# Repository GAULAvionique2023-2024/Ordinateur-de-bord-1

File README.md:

# ODB 1

## Description of the flight computer 1:
This board is an updated version of the first flight controler with little extra. So basicly I copy the old desing that it was an arduino shield and made it a standalone board. All the sensor is part of the board too, so no more module.All this help to make a board much smaller and more reliable. In extra I add a latching circuit too arme the board. You need to hold the button 3sec to power up the circuit and same thing to power it off. All switching is made with an mosfet so no mecanical switching excluding the power button. So the vibration can't make or break a connection and this is why the push button have an latching circuit, too avoid a false triger. Moreover I add a circuit too datalog the data on an SD card,I made a test circuit to test the 2 pyro. The circuit pass a little current (40mA) in the fuse and we mesure the voltage after so we can test for a short or open fuse. We can use this same circuit after to valid an ignition. I also add a logic circuit too avoid to put main power in the pyro when we trigger the test. It need 2 mosfet to be activate to ignite the fuse. A buzzer and a led status is also added. The board is powerd by a usb or lipo 1S(3.7v) that it can be charge by usb on the board. The RFD900 is powered by usb if its available but we will not be able to use full power only on usb so this is for testing only, on normal condition we will use an lipo 3S(11.1v). The pyro is powered by an lipo 4S(14.8v).

## Update log

### 23/12/16
All the test is now done. I corrected some mistake and change the status LED for an RGB one so it will be easier to understand its meaning. The new board its on the way.

### 23/11/22
Long time no see. Well I receive the board and do some test. All work except the GYRO and the inition of the fuse need to be confirm. I think I broke the gyro when I solder it so am waiting for a new one and in the same time im waiting for some e-fuse. I also made some minor change in the schematic and the board desing. Like switching the green status led by an RGB led, so it will be easyer to understand some status.  

### 23/10/09
Now the pcb is finish. I add the BOM file and the pcb is now on production.(see image: [ODB1_PCB](https://github.com/GAULAvionique2023-2024/Ordinateur-de-bord-1/blob/main/Images/ODB1_PCB.png))

### 23/10/01
So I rework the schematic to use less components and had the crystal circut, cause I dont know how but I was forgeting it. I also begin to layout the components on the pcb (see image: [OBD1_1_10_23](https://github.com/GAULAvionique2023-2024/Ordinateur-de-bord-1/blob/main/Images/OBD1_1_10_23.png)). I try my best to fit in the 85mmx85mm.

### 23/09/23
I add the possibility to use the RFD900 with the USB.

### 23/09/22
I can say that the schematic is now done but it will need to be verified to but sure that everything is ok and avoid poor mistake.
1.Redesing of the logic circuit protection to be more secure
2.Add a different batteries for the RFD900 so if the RFD900 drain it the pyro still have its own power.
3.In link with the second point, now the pyro is on 4s lipo (14.8v)

### 23/09/17
The schematic is almost done. Need to retink of some part of the logic part to protect the pyro cause it look like it can cause an oscilation (this part is not even up to date)
1.Add a buzzer.
2.Add poly fuse.
3.Add the logic circuit to protect the pyro. (see note on top)
4.Add latching circuit. (Hold 3s to power on/off)
5.Add many status leds. (one led can be placed externaly by a screw terminal)

This week I will try to list all the feature of this board, finalyze the schematic, add the data sheets of some ICs.

## Features
* Standalone board
* Powered by usb or lipo 1S
* Lipo charger in board
* Self test on igniter
* 2 ignitions circuits
* Gyro/Baro in board
* SD card for dataloging
* Latching circuit for powered the circuit
## Documentation
This is a list of documentation for the Ic

* [STM32F103C8](https://www.st.com/resource/en/datasheet/stm32f103c8.pdf) Main  microcontroller
* [ICM-20602](https://invensense.tdk.com/wp-content/uploads/2016/10/DS-000176-ICM-20602-v1.0.pdf) High Performance 6-Axis MEMS
* [BMP280](https://www.bosch-sensortec.com/media/boschsensortec/downloads/datasheets/bst-bmp280-ds001.pdf) Digital pressure sensor
* [L76L-M33](https://github.com/ul-gaul/Nebula-2022-2023/blob/cef41a131481a57f440abe9ede77973086518a58/WIP/Documentation/Quectel_L76_Series_Hardware_Design_V3.1.pdf) GNSS Module (GPS)
* [GT-0930RP2](https://github.com/ul-gaul/Nebula-2022-2023/blob/aa67e142a6133a87d8f8f1008be1e9982ea42536/WIP/Documentation/GT-0930RP2-14-Feb-2019.pdf) Buzzer
* [HM-10](https://github.com/ul-gaul/Nebula-2022-2023/blob/aa67e142a6133a87d8f8f1008be1e9982ea42536/WIP/Documentation/11.%20HM10%20BLE_FTDI.pdf)  BLE Module
* [TPS61201DRCR](https://www.ti.com/lit/ds/symlink/tps61201.pdf?ts=1695532721814&ref_url=https%253A%252F%252Fwww.ti.com%252Fproduct%252FTPS61201%252Fpart-details%252FTPS61201DRCR)  Low Input Voltage Synchronous Boost Converter
* [LM1085](https://www.ti.com/lit/ds/symlink/lm1085.pdf?ts=1695467476779&ref_url=https%253A%252F%252Fwww.ti.com%252Fproduct%252FLM1085%252Fpart-details%252FLM1085ISX-3.3%252FNOPB) 3-A Low Dropout Positive Regulators
* [max1898eub42+T](https://www.analog.com/media/en/technical-documentation/data-sheets/max1898.pdf) Linear Charger for Single-Cell Li+ Battery
* [LTC2954ITS8-1](https://www.analog.com/media/en/technical-documentation/data-sheets/2954fb.pdf) Pushbutton On/Off Controller with µP Interrup
* [CD74HC4051-EP](https://www.ti.com/lit/ds/symlink/cd74hc4051-ep.pdf?ts=1695467019480&ref_url=https%253A%252F%252Fwww.google.com%252F) Analog Multiplexer and Demultiplexer
* [74HC2G86DP_125](https://assets.nexperia.com/documents/data-sheet/74HC_HCT2G86.pdf) Dual 2-input EXCLUSIVE-OR gate
* [74HC2G86DP_125](https://assets.nexperia.com/documents/data-sheet/74HC_HCT2G08.pdf) Dual 2-input AND gate
* [74HC2G86DP_125](https://assets.nexperia.com/documents/data-sheet/74LVC2G02.pdf) Dual 2-input NOR gate

## Authors
List of authors
- [@Luka Dupuis](https://github.com/bestrider14)

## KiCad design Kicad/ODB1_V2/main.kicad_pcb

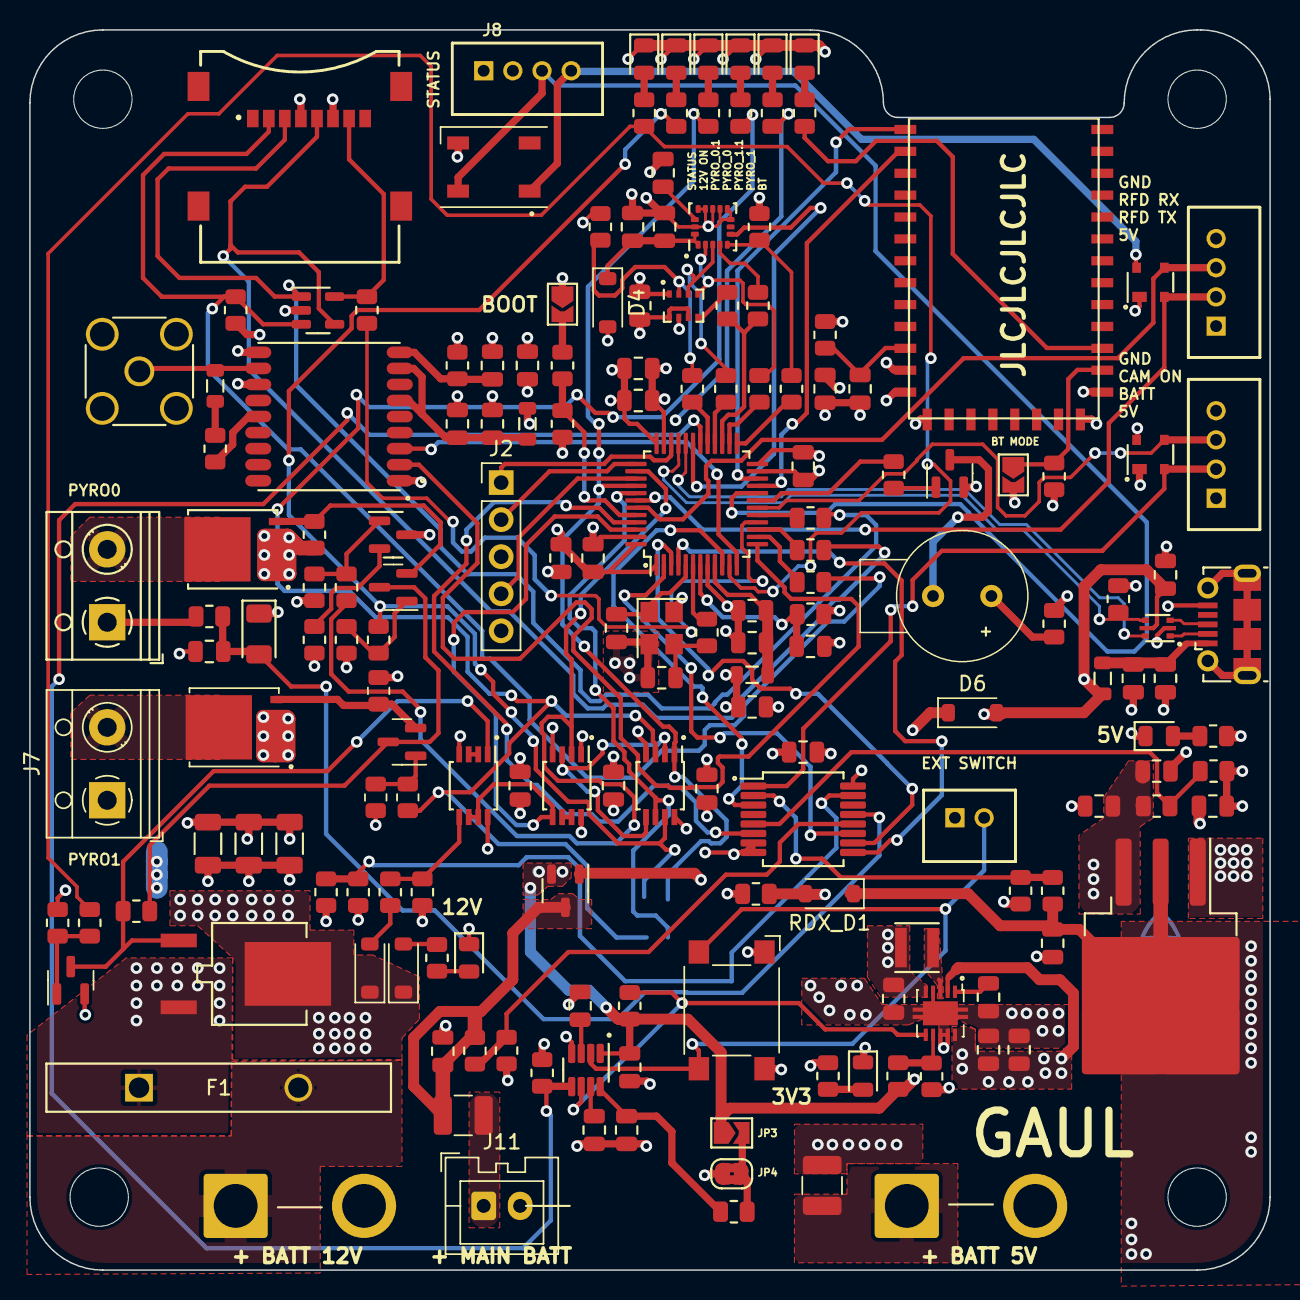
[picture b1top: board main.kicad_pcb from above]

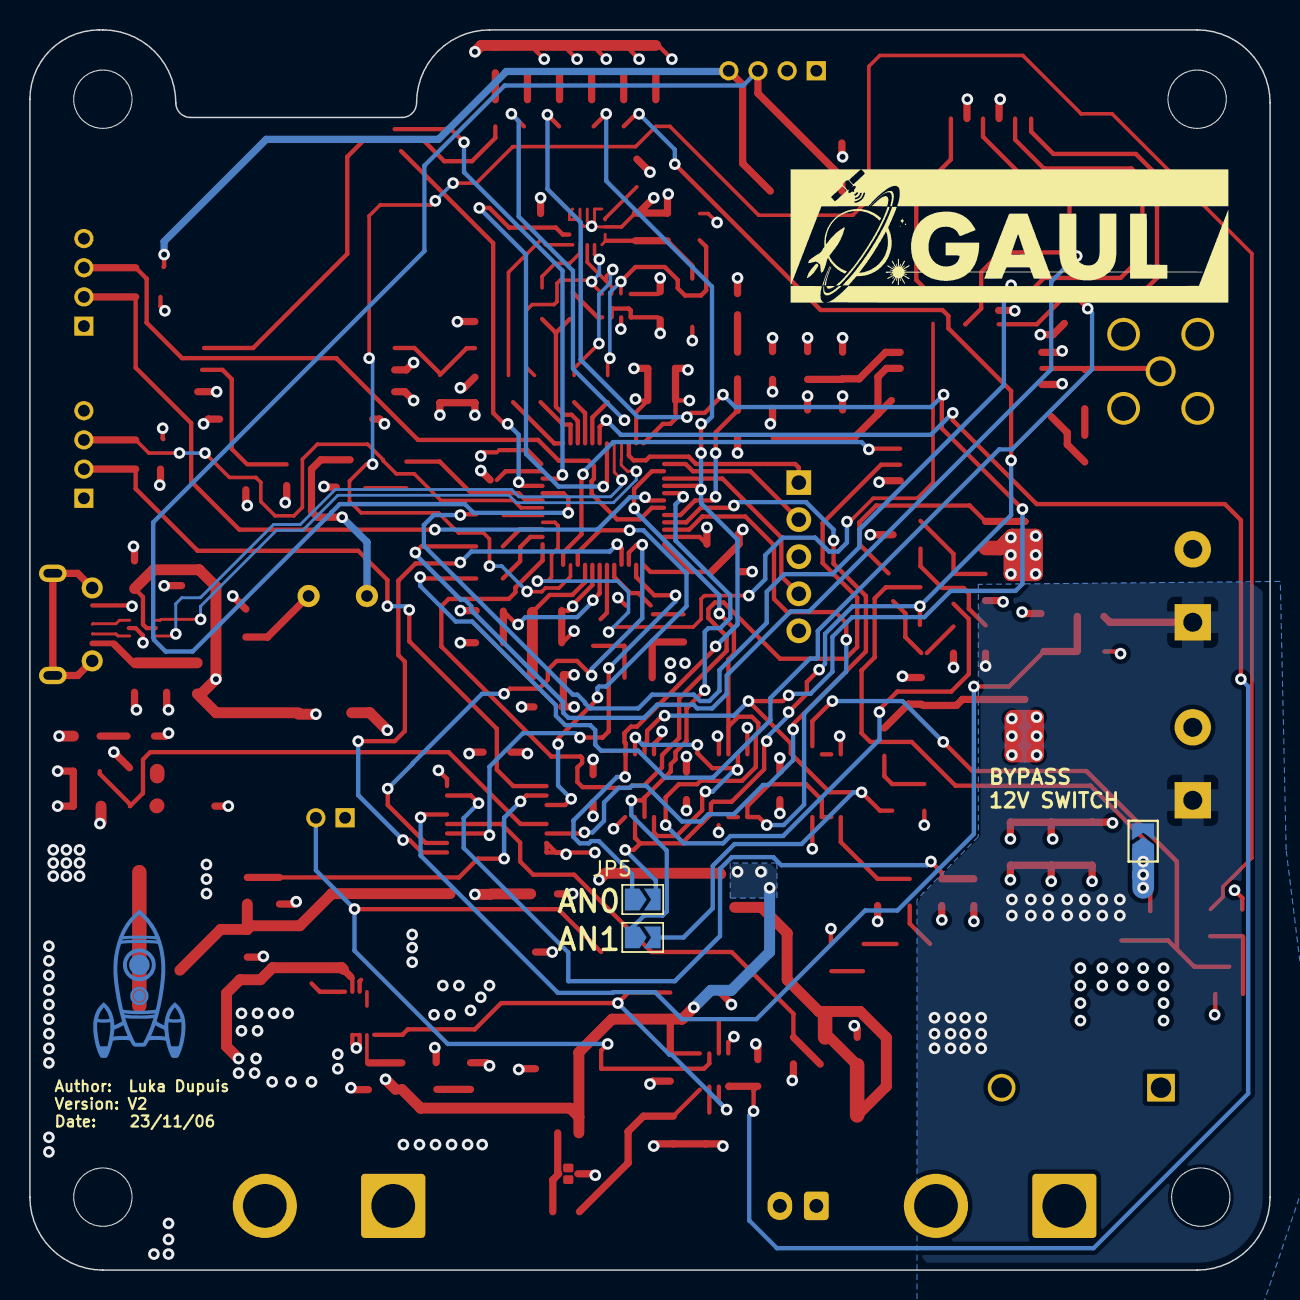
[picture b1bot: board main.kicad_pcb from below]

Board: 4 copper layers, 85.0 x 85.0 mm, 183 parts (3 on the bottom side), 122 nets.

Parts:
5V_R1: 56k; R_0805_2012Metric
5V_R2: 100k; R_0805_2012Metric
5V_R3: 1k5; R_0805_2012Metric
BATT1S_R13, BATT3S2_R12, BATT3S_R9: 100k; R_0805_2012Metric
BATT1S_R14: 27k; R_0805_2012Metric
BATT3S2_Q2: MMBT3904-TP; SOT-23
BATT3S2_R1, BATT3S2_R3, BATT3S2_R4, BATT3S2_R5: 10k; R_0805_2012Metric
BATT3S2_R2, BATT3S2_R6, BATT3S2_R7: 1k5; R_0805_2012Metric
BATT3S2_R11, BATT3S_R8: 36k; R_0805_2012Metric
BMP_C1: 10nf; C_0805_2012Metric
BMP_R1: 10k; R_0805_2012Metric
BMP_R2, BMP_R3: 10R; R_0805_2012Metric
BT_C1: 100nf; C_0805_2012Metric
BT_C2: 10uf; C_0805_2012Metric
BT_R1, BT_R2: 1k5; R_0805_2012Metric
BT_R3: 10k; R_0805_2012Metric
BUZ_R1: 1k5; R_0805_2012Metric
BUZ_R2: 30R; R_0805_2012Metric
BZ1: Buzzer; GT-0930RP2
C1: 10uf; C_0805_2012Metric
D1, D2: SP0503BAHTG; SOT-143
D3, D16: MMSZ4691-TP; D_SOD-123
D4, D6: B260A-13-F; D_SOD-123
D5: WS2812B; LED_WS2812B_PLCC4_5.0x5.0mm_P3.2mm
D8: SP0504BAHTG; SOT-23-5
E1: HM-10; 26.9X13X2.2_BOARD
F1: RGEF1400; FUS_RGEF1400_TYCO_TYC
F2, F3: 0ZCH0075AF2E (750ma); Fuse_1210_3225Metric
FB1, FB2, FB3: 120R; L_0805_2012Metric
GPS_C1, GPS_C3: 10uf; C_0805_2012Metric
GPS_C2, GPS_C4: 100nf; C_0805_2012Metric
GPS_R1: 10k; R_0805_2012Metric
GPS_R2: 10R; R_0805_2012Metric
H1, H2, H3, H4: MountingHole; MountingHole_4mm
ICM_C1, ICM_C4, ICM_C5: 100nf; C_0805_2012Metric
ICM_C2, ICM_C7: 10uf; C_0805_2012Metric
ICM_C6: 1uf; C_0805_2012Metric
ICM_R1: 10k; R_0805_2012Metric
ICM_R2, ICM_R3: 10R; R_0805_2012Metric
J1: RFD900; B4B-PH-K
J2: Conn_01x05_Socket; PinHeader_1x05_P2.54mm_Vertical
J3: USB_B_Micro; USB_Micro-B_Molex-105017-0001
J4: MEM2067-02-180-00-A_REVB; GCT_MEM2067-02-180-00-A_REVB
J5: RF2-04A-T-00-50-G; SMA_Wurth_60312002114503_Vertical
J6: PYRO0; TerminalBlock_RND_205-00012_1x02_P5.00mm_Horizontal
J7: PYRO1; TerminalBlock_RND_205-00012_1x02_P5.00mm_Horizontal
J8, J13: CAM; B4B-PH-K
J9: BATT3S1; SolderWire-2.5sqmm_1x02_P8.8mm_D2.4mm_OD4.4mm
J10: BATT12V; SolderWire-2.5sqmm_1x02_P8.8mm_D2.4mm_OD4.4mm
J11: BATT1S; JST_XA_B02B-XASK-1_1x02_P2.50mm_Vertical
J12: EXT_SW; B2B-PH-K
JP1, JP2, JP3, JP5, JP6, JP7: SolderJumper_2_Open; SolderJumper-2_P1.3mm_Open_TrianglePad1.0x1.5mm
JP4: SolderJumper_2_Bridged; SolderJumper-2_P1.3mm_Bridged2Bar_RoundedPad1.0x1.5mm
L1: 100nH; L_0805_2012Metric
LED_3S2_ON1, LED_3V3, LED_5V1, LED_14V8: GREEN; LED_0805_2012Metric
LED_BT1: GREEN; LED_0805_2012Metric
LED_PYRO_0, LED_PYRO_0.1, LED_PYRO_1, LED_PYRO_1.1: GREEN; LED_0805_2012Metric
LPWR_L1: 3.3uH; IND_LQH3NPN3R3MMEL
LTC_C1, LTC_C2: 100nf; C_0805_2012Metric
LTC_C3, LTC_C4: 0.47uf; C_0805_2012Metric
LTC_R1, LTC_R2, LTC_R3: 10k; R_0805_2012Metric
NRST_C1: 100nf; C_0805_2012Metric
PWR_C1: 33uf; C_0805_2012Metric
PWR_C2, PWR_C4, PWR_C5: 10uf; C_0805_2012Metric
PWR_C3, PWR_C8, PWR_C9, PWR_C11: 100nf; C_0805_2012Metric
PWR_C6: 10uf; C_1206_3216Metric
PWR_C7: 100nf; C_1206_3216Metric
PWR_C10: 33uf; C_1206_3216Metric
PWR_R1: 1k5; R_0805_2012Metric
PWR_R2: 1.87M; R_0805_2012Metric
PWR_R3: 249k; R_0805_2012Metric
PYRO_Q3, PYRO_Q211: MMBT3904-TP; SOT-23
PYR_C1, PYR_C3, PYR_C4, PYR_C5, PYR_C6: 100nf; C_0805_2012Metric
PYR_D1: SM5817PL-TP; D_1206_3216Metric
PYR_R2, PYR_R6, PYR_R9, PYR_R13, PYR_R14, PYR_R15, PYR_R16: 1k5; R_0805_2012Metric
PYR_R3, PYR_R5, PYR_R17, PYR_R18, PYR_R19: 10k; R_0805_2012Metric
PYR_R4: 130R 1%; R_0805_2012Metric
PYR_R7: 56k; R_0805_2012Metric
Q2: PMOS; SOT-23-3
Q3, Q8: CSD17310Q5A; TDSON-8-1
Q4: MMBT3904; SOT-23
Q5: IRFR5505TRPBF; PG-TO252AA_INF
Q6: BC857; SOT-23
R2: 100k; R_0805_2012Metric
RDX_D1: B260A-13-F; D_SOD-123
RSTM_R2: 1k5; R_0805_2012Metric
SDC_R1: 10k; R_0805_2012Metric
SDC_R2, SDC_R3, SDC_R4, SDC_R5: 10R; R_0805_2012Metric
SPI_R2, SPI_R3: 10R; R_0805_2012Metric
STM_C1, STM_C6: 10uf; C_0805_2012Metric
STM_C2, STM_C3, STM_C4, STM_C5: 100nf; C_0805_2012Metric
STM_C7, STM_C8: 10nf; C_0805_2012Metric
STM_C9, STM_C10: 6p; C_0805_2012Metric
STM_R1, STM_R3: 10k; R_0805_2012Metric
STM_R4: 30R; R_0805_2012Metric
SW1: POWER BUTTON; SW_SPST_Omron_B3FS-105xP
U1: STM32F103CBT6; LQFP-48_7x7mm_P0.5mm
U2: ICM-20602; LGA-16_3x3mm_P0.5mm_LayoutBorder3x5y
U3: BMP280; Bosch_LGA-8_2x2.5mm_P0.65mm_ClockwisePinNumbering
U4: L76L-M33; GNSS-MODULE_L76L-M33
U5: TPS61201DRCR; VSON-10-1EP_3x3mm_P0.5mm_EP1.65x2.4mm
U7: 74HC4051; SSOP-16_5.3x6.2mm_P0.65mm
U8: LM1085-5.0; TO-263-3_TabPin2
U9: 74HC2G08DP,125; TSSOP-8_3x3mm_P0.65mm
U10: 74LVC2G02DP,125; TSSOP-8_3x3mm_P0.65mm
U11: LTC2954ITS8-1; TSOT-23-8
U12: USBLC6-2P6; SOT-666
U13: 74HC2G86DP_125; TSSOP-8_3x3mm_P0.65mm
USB_R1: 1k5; R_0805_2012Metric
Y1: 16mhz; Crystal_SMD_3225-4Pin_3.2x2.5mm

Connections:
3V3_EN: LTC_R1.1, U5.6 (EN), U11.6 (EN)
5V_AN: 5V_R1.2, 5V_R2.2, U7.2 (A6)
12V_CHECK: U1.46 (PB9), U10.6 (2B), U10.7 (1Y), U13.5 (2A)
+3.3VA: FB3.1, STM_C6.2, STM_C7.2, U1.9 (VDDA)
+3V3: BMP_C1.1, BMP_R1.1, BT_C2.1, BT_R2.2, BT_R3.1, BUZ_R2.1, D4.2 (A), E1.12 (+3.3V), FB1.2, FB3.2, GPS_C3.2, GPS_R1.2, ICM_R1.1, J2.3, J4.4 (VDD), JP1.1 (A), JP4.1 (A), LTC_R3.1, PWR_C1.1, PWR_C8.1, PWR_R1.1, PYR_C3.1, PYR_C4.1, PYR_C5.2, PYR_C6.1, PYR_D1.1 (K), PYR_R5.1, Q6.3 (C), SDC_R1.2, STM_C1.2, STM_C2.2, STM_C3.2, STM_C4.2, STM_C5.2, STM_C8.2, STM_R1.2, U1.1 (VBAT), U1.24 (VDD), U1.36 (VDD), U1.48 (VDD), U3.6 (VDDIO), U3.8 (VDD), U5.2 (VOUT), U5.10 (FB), U7.16 (VCC), U9.8 (VCC), U10.8 (VCC), U13.1 (1A), U13.8 (VCC), USB_R1.2
+5V: 5V_R1.1, 5V_R3.1, D1.4 (K), D2.4 (K), D5.1 (VDD), J1.1, J8.4, J13.1, PWR_C5.1, PWR_C11.1, RDX_D1.1 (K), U8.2 (VO)
+12C: BATT3S2_R1.1, BATT3S2_R12.2, F1.1, JP6.1 (A), PWR_C6.1, PWR_C7.1, PWR_C10.1, PYRO_Q3.3 (C), PYRO_Q211.3 (C), Q5.3 (S)
+12P: BATT3S_R9.2, F3.1, PWR_C4.1, PWR_C9.1, U8.3 (VI)
+12V: D3.1 (K), D16.1 (K), J6.1, J7.1, JP6.2 (B), PYR_R4.1, PYR_R7.1, Q5.2 (D)
+BATT: BATT1S_R14.2, C1.1, F2.1, Q2.3 (D)
/Power/12IN: F1.2, J10.1
BATT3S2_ON: BATT3S2_R2.1, BATT3S2_R7.1, U1.11 (PA1)
BATT_CAM: D2.2 (K), J13.2, U7.1 (A4)
BATT_LIPO1S_AN: BATT1S_R13.2, BATT1S_R14.1, U7.12 (A3)
BATT_LIPO3S2_AN: BATT3S2_R11.2, BATT3S2_R12.1, U7.15 (A2)
BATT_LIPO3S_AN: BATT3S_R8.2, BATT3S_R9.1, U7.5 (A5)
BMP_CS: BMP_R1.2, BMP_R2.2, U3.2 (CSB)
BOOT0: RSTM_R2.1, STM_R3.2, U1.44 (BOOT0)
BT_RX: E1.1 (UART_TX), U1.22 (PB11)
BT_TX: E1.2 (UART_RX), U1.21 (PB10)
BUTTON_INT: LTC_R3.2, U1.30 (PA9), U11.5 (*INT)
BUZZER: BUZ_R1.1, U1.19 (PB1)
CAM_ON: D2.3 (K), J13.3, U1.18 (PB0)
FLIP_FLOP_RST: BATT3S2_R1.2, Q4.3 (C), Q5.1 (G), U10.1 (1A)
FLIP_FLOP_SET: BATT3S2_R4.1, BATT3S2_R5.1, U10.5 (2A)
GND: 5V_R2.1, BATT1S_R13.1, BATT3S2_Q2.2 (E), BATT3S2_R3.1, BATT3S2_R5.2, BATT3S2_R11.1, BATT3S_R8.1, BMP_C1.2, BT_C1.2, BT_C2.2, C1.2, D1.1 (A), D2.1 (A), D5.3 (VSS), D8.2 (A), E1.13 (GND), E1.14 (GND), E1.21 (GND), E1.22 (GND), GPS_C1.1, GPS_C2.1, GPS_C3.1, GPS_C4.1, ICM_C1.1, ICM_C2.1, ICM_C4.2, ICM_C5.1, ICM_C6.1, ICM_C7.1, J1.4, J2.5, J3.5 (GND), J4.6 (VSS), J5.2 (Ext), J8.2, J9.2, J10.2, J11.2, J12.1, J13.4, JP2.2 (B), LED_3S2_ON1.1 (K), LED_3V3.1 (K), LED_5V1.1 (K), LED_14V8.1 (K), LED_BT1.1 (K), LED_PYRO_0.1 (K), LED_PYRO_0.1.1 (K), LED_PYRO_1.1 (K), LED_PYRO_1.1.1 (K), LTC_C1.2, LTC_C2.2, LTC_C3.2, LTC_C4.2, NRST_C1.2, PWR_C1.2, PWR_C2.2, PWR_C3.2, PWR_C4.2, PWR_C5.2, PWR_C6.2, PWR_C7.2, PWR_C8.2, PWR_C9.2, PWR_C10.2, PWR_C11.2, PWR_R3.2, PYR_C1.2, PYR_C3.2, PYR_C4.2, PYR_C5.1, PYR_C6.2, PYR_R3.1, PYR_R17.1, PYR_R18.1, PYR_R19.1, Q3.1 (S), Q3.2 (S), Q3.3 (S), Q4.2 (E), Q8.1 (S), Q8.2 (S), Q8.3 (S), R2.2, STM_C1.1, STM_C2.1, STM_C3.1, STM_C4.1, STM_C5.1, STM_C6.1, STM_C7.1, STM_C8.1, STM_C9.1, STM_C10.1, STM_R3.1, SW1.1, U1.8 (VSSA), U1.23 (VSS), U1.35 (VSS), U1.47 (VSS), U2.8 (FSYNC), U2.9 (GND), U2.10 (GND), U2.11 (GND), U2.12 (GND), U2.13 (GND), U2.15 (GND), U3.1 (GND), U3.7 (GND), U4.1 (GND), U4.10 (GND), U4.12 (GND), U5.4 (PGND), U5.8 (PS), U5.9 (GND), U5.11 (EP), U7.7 (VEE), U7.8 (GND), U8.1 (GND), U9.4 (GND), U10.4 (GND), U11.4 (GND), U12.2 (GND), U13.4 (GND), Y1.2, Y1.4
GPS_RF: J5.1 (In), L1.1, U4.11 (RF_IN)
GPS_RX: U1.13 (PA3), U4.2 (TXD1)
GPS_TX: U1.12 (PA2), U4.3 (RXD1)
ICM_CS: ICM_R1.2, ICM_R3.2, U2.5 (~CS)
ICM_INT: U1.31 (PA10), U2.6 (INT)
LED_STATUS: D5.4 (DIN), J8.3, U1.20 (PB2)
MUL_AN: U1.10 (PA0), U7.3 (A)
MUL_E~: U1.45 (PB8), U7.6 (~E)
MUL_S0: U1.2 (PC13), U7.11 (S0)
MUL_S1: U1.3 (PC14), U7.10 (S1)
MUL_S2: U1.4 (PC15), U7.9 (S2)
NRST: NRST_C1.1, STM_R1.1, U1.7 (NRST)
unnamed: BATT3S2_Q2.1 (B), BUZ_R1.2
unnamed: BATT3S2_Q2.3 (C), BZ1.2 (+)
unnamed: BUZ_R2.2, BZ1.1 (-)
unnamed: BATT3S2_R6.2, D3.2 (A)
unnamed: D4.1 (K), ICM_C1.2, ICM_C2.2, U2.1 (VDDIO), U2.16 (VDD)
unnamed: BATT3S2_R4.2, D16.2 (A)
unnamed: BT_R2.1, E1.23 (KEY), JP2.1 (A)
unnamed: BT_R1.1, E1.24 (LED)
unnamed: BT_C1.1, BT_R3.2, E1.11 (RESET)
unnamed: GPS_R2.1, L1.2
unnamed: D8.5 (K), J4.7 (DAT0), SDC_R5.2
unnamed: J6.2, Q8.5 (D)
unnamed: J7.2, Q3.5 (D)
unnamed: F3.2, J9.1
unnamed: F2.2, J11.1
unnamed: J12.2, SW1.2, U11.2 (*PB)
unnamed: JP1.2 (B), RSTM_R2.2
unnamed: JP3.2 (B), JP4.2 (B), LTC_R2.1
unnamed: BATT3S2_R7.2, LED_3S2_ON1.2 (A)
unnamed: LED_3V3.2 (A), PWR_R1.2
unnamed: 5V_R3.2, LED_5V1.2 (A)
unnamed: BATT3S2_R6.1, LED_14V8.2 (A)
unnamed: BT_R1.2, LED_BT1.2 (A)
unnamed: LED_PYRO_0.2 (A), PYR_R15.2
unnamed: LED_PYRO_0.1.2 (A), PYR_R13.2
unnamed: LED_PYRO_1.2 (A), PYR_R16.2
unnamed: LED_PYRO_1.1.2 (A), PYR_R14.2
unnamed: PYRO_Q3.1 (B), PYR_R9.1, PYR_R18.2
unnamed: PYRO_Q3.2 (E), PYR_R19.2, Q3.4 (G)
unnamed: PYRO_Q211.1 (B), PYR_R2.1, PYR_R3.2
unnamed: PYRO_Q211.2 (E), PYR_R17.2, Q8.4 (G)
unnamed: BATT3S2_R2.2, BATT3S2_R3.2, Q4.1 (B)
unnamed: PYR_R5.2, PYR_R6.1, Q6.1 (B)
unnamed: PYR_R4.2, Q6.2 (E)
unnamed: STM_C10.2, STM_R4.2, Y1.3
unnamed: SDC_R2.1, U1.14 (PA4)
unnamed: SDC_R4.1, U1.15 (PA5)
unnamed: SDC_R3.1, U1.17 (PA7)
unnamed: BMP_R2.1, U1.29 (PA8)
unnamed: ICM_R3.1, U1.25 (PB12)
unnamed: SPI_R2.1, U1.26 (PB13)
unnamed: SPI_R3.1, U1.28 (PB15)
unnamed: ICM_C4.1, U2.14 (REGOUT)
unnamed: ICM_R2.1, U2.4 (SAO/SD0)
unnamed: BMP_R3.1, U3.5 (SDO)
unnamed: GPS_C4.2, GPS_R1.1, U4.9 (RESET)
unnamed: FB1.1, GPS_C1.2, GPS_C2.2, U4.6 (V_BCKP), U4.8 (VCC)
unnamed: GPS_R2.2, U4.14 (VCC_RF)
unnamed: LPWR_L1.2, U5.3 (L)
unnamed: PWR_R2.2, PWR_R3.1, U5.7 (UVLO)
unnamed: PWR_C3.1, U5.1 (VAUX)
unnamed: U10.2 (1B), U10.3 (2Y)
unnamed: LTC_C2.1, LTC_R2.2, U11.8 (*KILL)
unnamed: LTC_C4.1, U11.3 (ONT)
unnamed: LTC_C3.1, U11.7 (PDT)
unnamed: U13.6 (2B), U13.7 (1Y)
unnamed: U9.2 (1B), U9.5 (2A), U13.3 (2Y)
PD0: STM_C9.2, U1.5 (PD0), Y1.1
PD1: STM_R4.1, U1.6 (PD1)
PYRO_AN0: PYR_C1.1, PYR_D1.2 (A), PYR_R7.2, U7.13 (A0)
PYRO_ON0: JP5.1 (A), PYR_R15.1, U1.40 (PB4), U9.1 (1A)
PYRO_ON0.1: JP5.2 (B), PYR_R2.2, PYR_R13.1, U9.7 (1Y)
PYRO_ON1: JP7.1 (A), PYR_R16.1, U1.41 (PB5), U9.6 (2B)
PYRO_ON1.1: JP7.2 (B), PYR_R9.2, PYR_R14.1, U9.3 (2Y)
PYRO_TEST~: PYR_R6.2, U1.38 (PA15), U13.2 (1B)
RFD_RX: D1.3 (K), J1.3, U1.43 (PB7)
RFD_TX: D1.2 (K), J1.2, U1.42 (PB6)
SDC_CS: D8.3 (K), J4.2 (CD/DAT3), SDC_R1.1, SDC_R2.2
SPI1_MISO: SDC_R5.1, U1.16 (PA6)
SPI1_MOSI: D8.1 (K), J4.3 (CMD), SDC_R3.2
SPI1_SCLK: D8.4 (K), J4.5 (CLK), SDC_R4.2
SPI2_MISO: BMP_R3.2, ICM_R2.2, U1.27 (PB14)
SPI2_MOSI: SPI_R3.2, U2.3 (SDA/SDI), U3.3 (SDI)
SPI2_SCLK: SPI_R2.2, U2.2 (SCL/SPC), U3.4 (SCK)
SYS_SWCLK: J2.2, U1.37 (PA14)
SYS_SWDIO: J2.1, U1.34 (PA13)
SYS_TRACESWO: J2.4, U1.39 (PB3)
USB_D+: U1.33 (PA12), U12.4 (I/O2), USB_R1.1
USB_D-: U1.32 (PA11), U12.6 (I/O1)
USB_D_CON+: J3.3 (D+), U12.3 (I/O2)
USB_D_CON-: J3.2 (D-), U12.1 (I/O1)
USB_VBUS: FB2.2, ICM_C6.2, ICM_C7.2, J3.1 (VBUS)
VCC: D6.1 (K), JP3.1 (A), LPWR_L1.1, LTC_C1.1, LTC_R1.2, PWR_C2.1, PWR_R2.1, Q2.2 (S), U5.5 (VIN), U11.1 (VIN)
VDD: D6.2 (A), FB2.1, ICM_C5.2, Q2.1 (G), R2.1, RDX_D1.2 (A), U12.5 (VBUS)

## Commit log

2023-10-05 clone ancien repos
2023-10-09 Add BOM file
2023-10-09 add image and BOM
2023-12-17 Rename _WIP_ODB1.rar to ODB1_V1.rar
2023-12-18 Rename schematic.pdf to schematic_v1.pdf
2023-12-19 /code/test
2023-12-19 Rename OBD1_TEST_CODE.rar to code/test/OBD1_TEST_CODE.rar
2024-01-26 Add base firmware
